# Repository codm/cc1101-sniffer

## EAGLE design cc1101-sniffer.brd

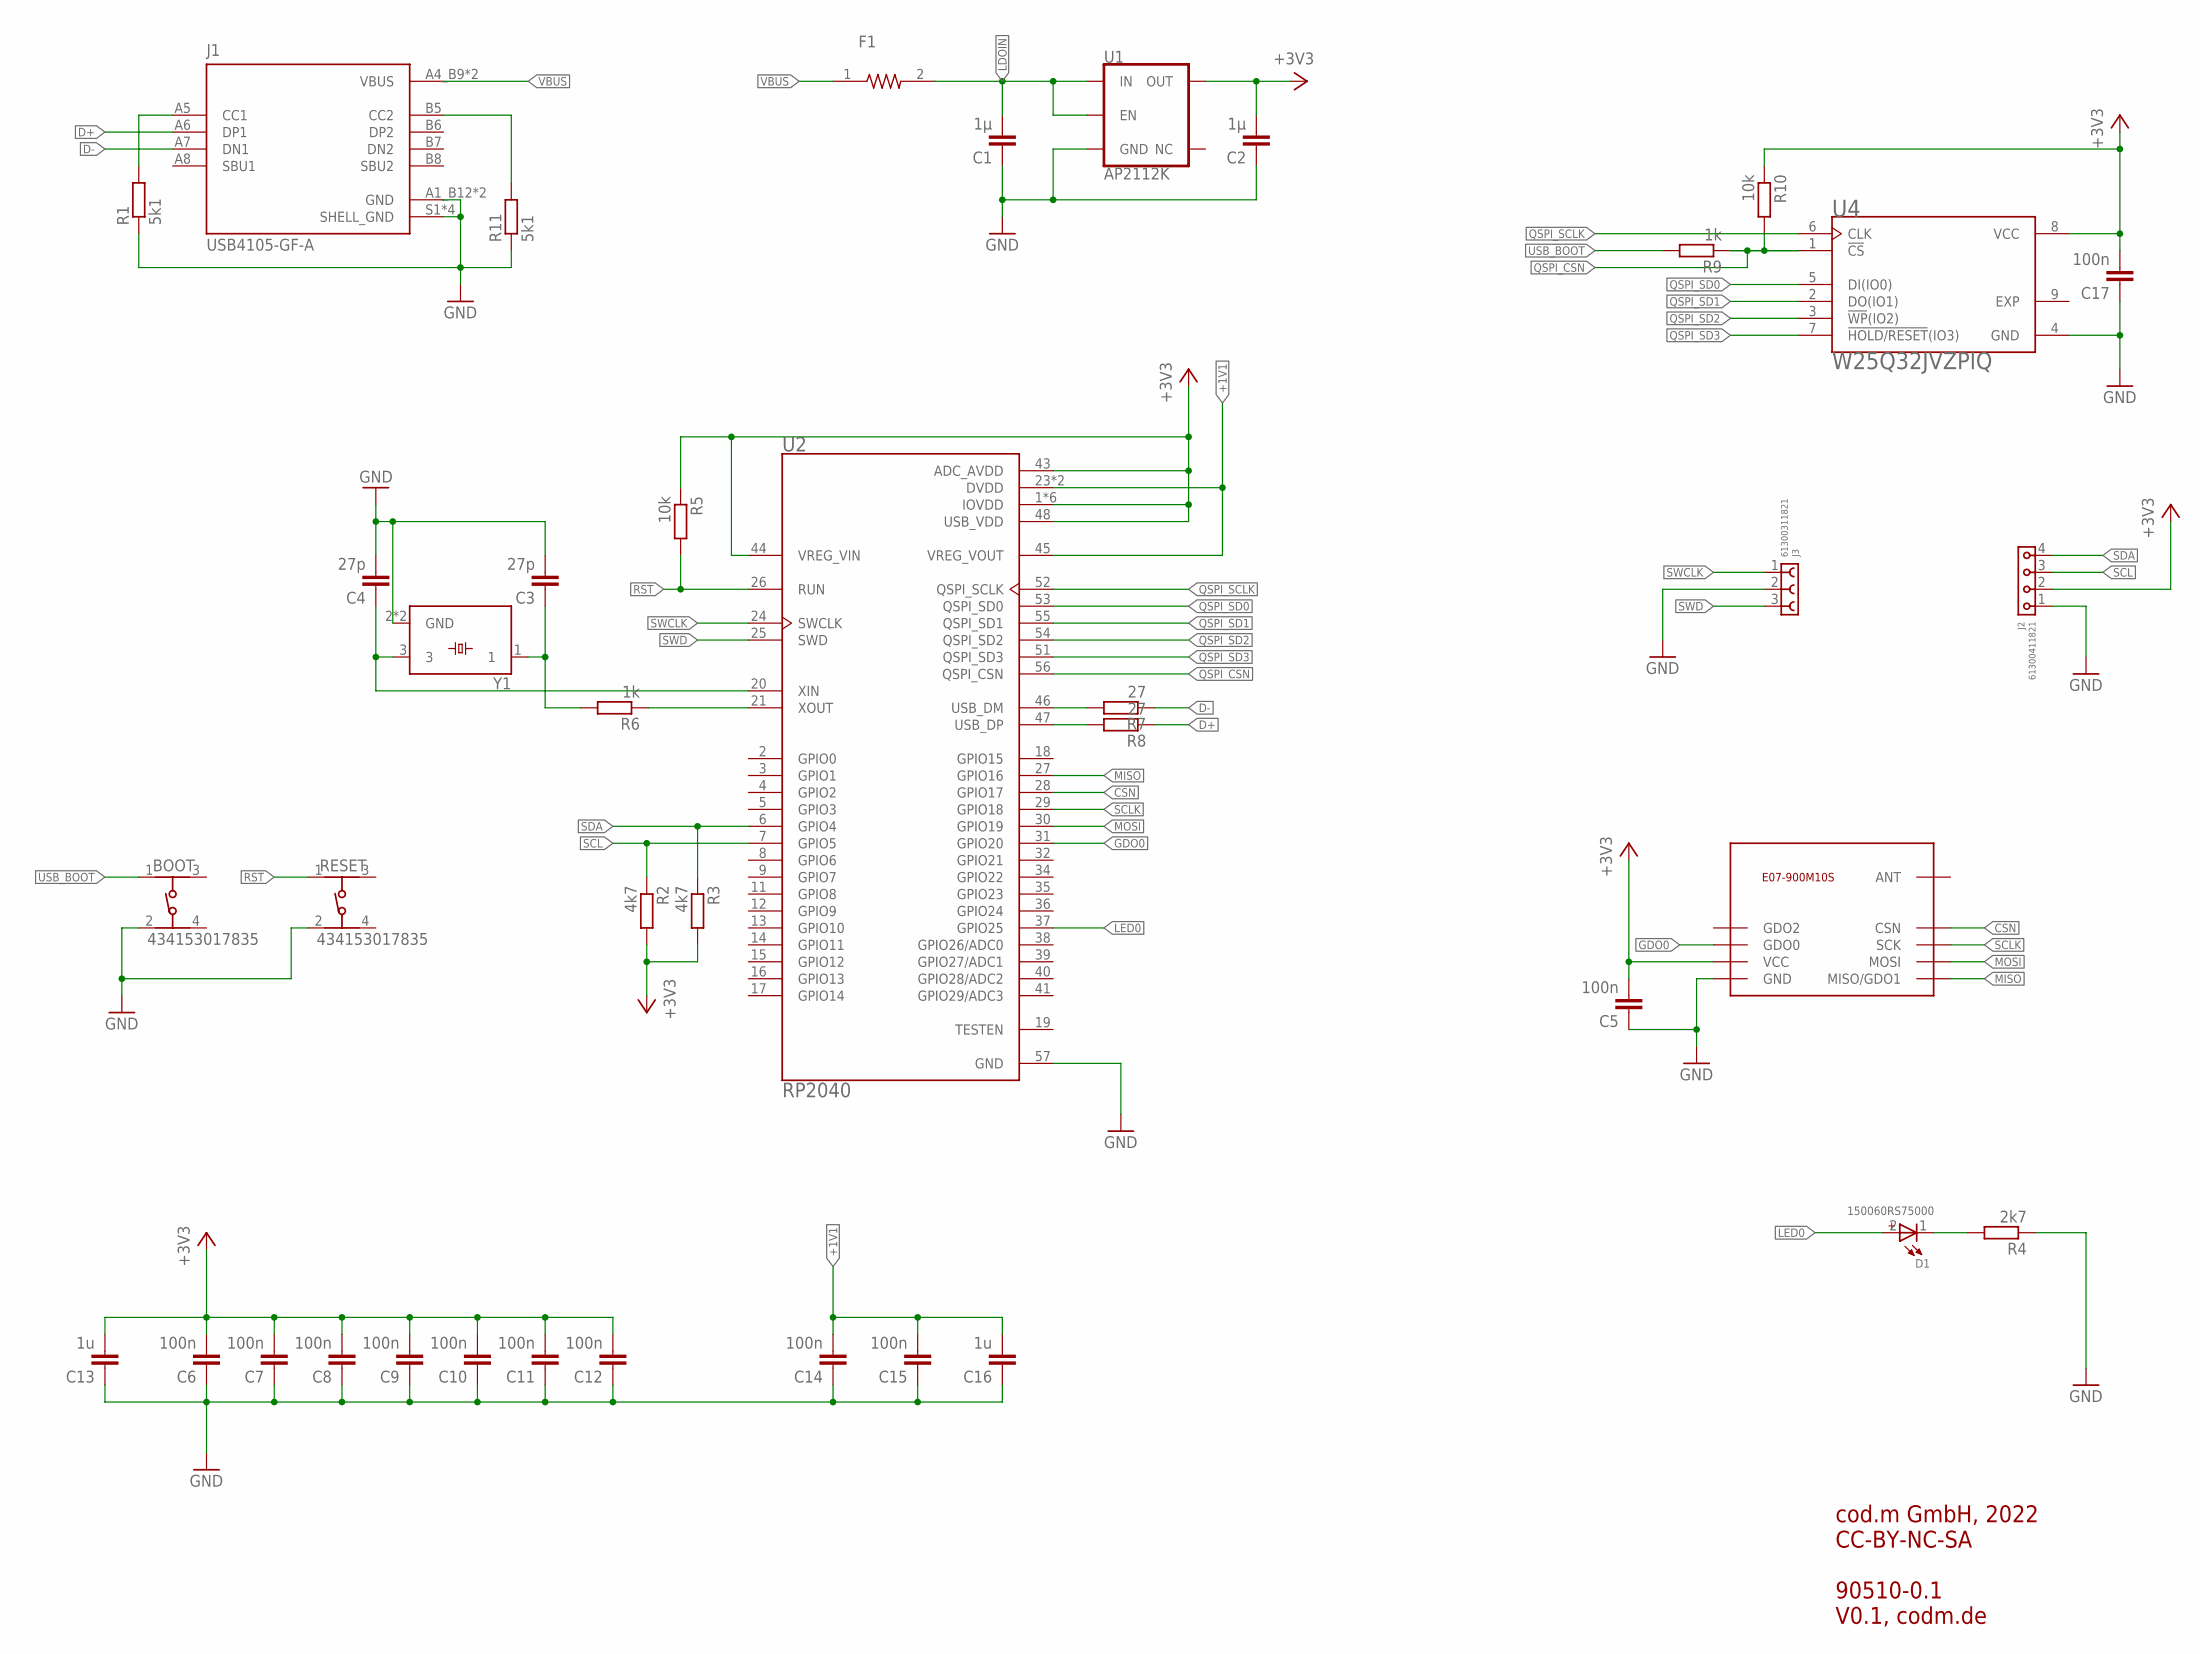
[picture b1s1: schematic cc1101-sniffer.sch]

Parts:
BOOT: 434153017835
C1, C2: 1µ; C0805K
C3, C4: 27p; C0603K
C5, C6, C7, C8, C9, C10, C11, C12, C14, C15, C17: 100n; C0603K
C13, C16: 1u; C0603K
D1: 150060RS75000; WL-SMCW_0603
F1: PICOSMDC050S-2; RESC2012X65N
J1: USB4105-GF-A; GCT_USB4105-GF-A
J2: 61300411821
J3: 61300311821
R1, R11: 5k1; R0603RF
R2, R3: 4k7; R0603RF
R4: 2k7; R0603RF
R5, R10: 10k; R0603RF
R6, R9: 1k; R0603RF
R7, R8: 27; R0603RF
RESET: 434153017835
U1: AP2112K; SOT23-5
U2: RP2040; QFN40P700X700X90-57N
U4: W25Q32JVZPIQ; SON127P600X500X80-9N
U$6: E07-900M10S
Y1: ABM8G-12.000MHZ-18-D2Y-T3; OSCSC320X250X100N

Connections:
+1V1: C14.2, C15.2, C16.2, U2.23 (DVDD), U2.45 (VREG_VOUT), U2.50 (DVDD)
+3V3: C2.2, C5.2, C6.2, C7.2, C8.2, C9.2, C10.2, C11.2, C12.2, C13.2, C17.2, J2.2, R2.2, R3.2, R5.1, R10.1, U1.5 (OUT), U2.1 (IOVDD), U2.10 (IOVDD), U2.22 (IOVDD), U2.33 (IOVDD), U2.42 (IOVDD), U2.43 (ADC_AVDD), U2.44 (VREG_VIN), U2.48 (USB_VDD), U2.49 (IOVDD), U4.8 (VCC), U$6.9 (VCC)
CSN: U2.28 (GPIO17), U$6.19 (CSN)
D+: J1.A6 (DP1), R8.1
D-: J1.A7 (DN1), R7.1
GDO0: U2.31 (GPIO20), U$6.15 (GDO0)
GND: BOOT.2 (3), C1.1, C2.1, C3.2, C4.2, C5.1, C6.1, C7.1, C8.1, C9.1, C10.1, C11.1, C12.1, C13.1, C14.1, C15.1, C16.1, C17.1, J1.A1_B12 (GND), J1.B1_A12 (GND), J1.S1 (SHELL_GND), J1.S2 (SHELL_GND), J1.S3 (SHELL_GND), J1.S4 (SHELL_GND), J2.1, J3.2, R1.1, R4.1, R11.1, RESET.2 (3), U1.2 (GND), U2.57 (GND), U4.4 (GND), U$6.1 (GND), U$6.2 (GND), U$6.3 (GND), U$6.4 (GND), U$6.5 (GND), U$6.11 (GND), U$6.12 (GND), U$6.20 (GND), U$6.22 (GND), Y1.2 (GND), Y1.4 (GND)
LDOIN: C1.2, F1.2, U1.1 (IN), U1.3 (EN)
LED0: D1.2 (+), U2.37 (GPIO25)
MISO: U2.27 (GPIO16), U$6.16 (MISO/GDO1)
MOSI: U2.30 (GPIO19), U$6.17 (MOSI)
unnamed: C4.1, U2.20 (XIN), Y1.3
unnamed: R6.1, U2.21 (XOUT)
unnamed: C3.1, R6.2, Y1.1
unnamed: R8.2, U2.47 (USB_DP)
unnamed: J1.A5 (CC1), R1.2
unnamed: D1.1 (-), R4.2
unnamed: R7.2, U2.46 (USB_DM)
unnamed: J1.B5 (CC2), R11.2
QSPI_CSN: R9.1, R10.2, U2.56 (QSPI_CSN), U4.1 (!CS)
QSPI_SCLK: U2.52 (QSPI_SCLK), U4.6 (CLK)
QSPI_SD0: U2.53 (QSPI_SD0), U4.5 (DI(IO0))
QSPI_SD1: U2.55 (QSPI_SD1), U4.2 (DO(IO1))
QSPI_SD2: U2.54 (QSPI_SD2), U4.3 (!WP!(IO2))
QSPI_SD3: U2.51 (QSPI_SD3), U4.7 (!HOLD/RESET!(IO3))
RST: R5.2, RESET.1, U2.26 (RUN)
SCL: J2.3, R2.1, U2.7 (GPIO5)
SCLK: U2.29 (GPIO18), U$6.18 (SCK)
SDA: J2.4, R3.1, U2.6 (GPIO4)
SWCLK: J3.1, U2.24 (SWCLK)
SWD: J3.3, U2.25 (SWD)
USB_BOOT: BOOT.1, R9.2
VBUS: F1.1, J1.A4_B9 (VBUS), J1.B4_A9 (VBUS)

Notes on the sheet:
cod.m GmbH, 2022 CC-BY-NC-SA 90510-0.1 V0.1, codm.de

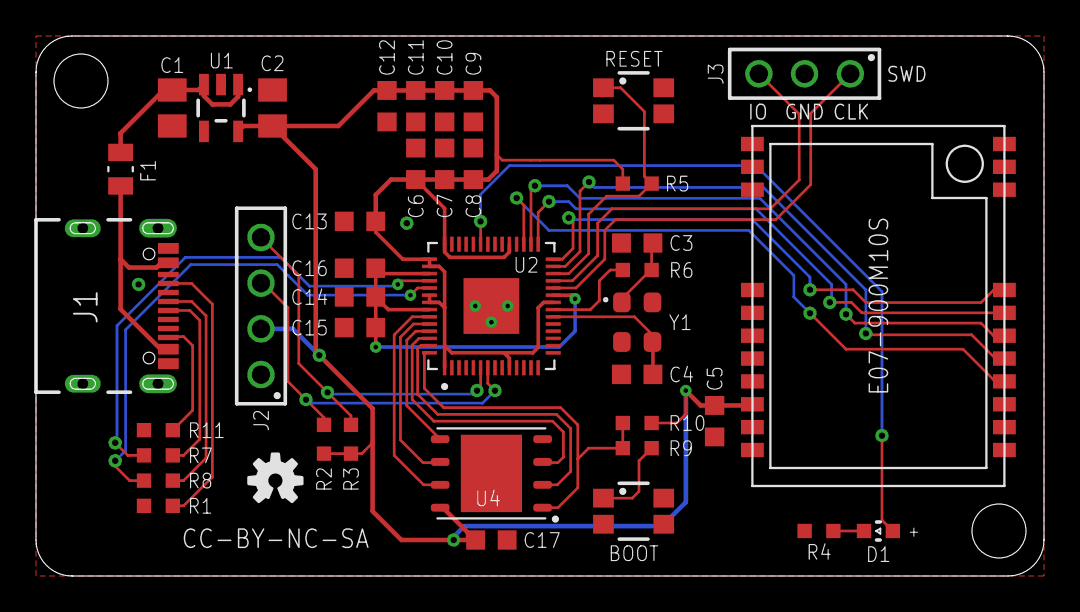
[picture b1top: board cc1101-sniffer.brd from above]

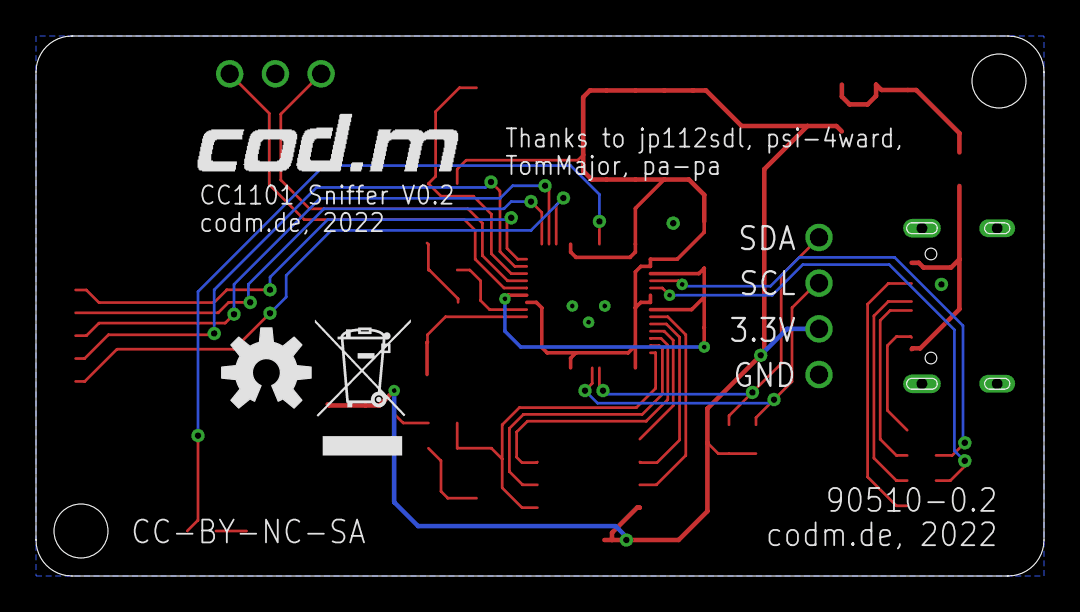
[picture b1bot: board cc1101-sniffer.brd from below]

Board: 2 copper layers, 56.0 x 30.0 mm, 44 parts (3 on the bottom side), 33 nets.

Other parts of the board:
U$1: WEEE-LOGO-5MM
U$3: OSHW-LOGO-M
U$4: OSHW-LOGO-S
U$5: CODM-LOGO

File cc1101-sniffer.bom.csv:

"Qty";"Value";"Device";"Package";"Parts";"Description";"AVAILABILITY";"CHIP-TECHNOLOGY";"DATASHEET-URL";"DESCRIPTION";"DOMINANT-WAVELENGTH";"EMITTING-COLOR";"FORWARD-VOLTAGE";"GENDER";"H";"IR";"LUMINOUS-INTENSITY";"MF";"MOUNT";"MP";"OPERATION-FORCE";"PACKAGE";"PACKAGING";"PART-NUMBER";"PEAK-WAVELENGTH";"PINS";"PITCH";"POPULARITY";"PRICE";"PROD_ID";"PURCHASE-URL";"QTY";"ROWS";"SPICEPREFIX";"TYPE";"VALUE";
"1";"";"ANTENNA_U.FL";"U.FL";"X1";"U.FL Antenna Connector";"";"";"";"";"";"";"";"";"";"";"";"";"";"";"";"";"";"";"";"";"";"";"";"";"";"";"";"";"";"";
"1";" 61300311821 ";"6130XX11821_61300311821";"61300311821";"J3";"WR-PHD 2.54 mm Socket Header";"";"";"https://www.we-online.com/catalog/datasheet/61300311821.pdf";"";"";"";"";"Socket Header";"";"3A";"";"";"THT";"";"";"";"Tray";" 61300311821 ";"";" 3 ";"2.54mm";"";"";"";"";"";"Single";"";"Straight";" 61300311821 ";
"1";" 61300411821 ";"6130XX11821_61300411821";"61300411821";"J2";"WR-PHD 2.54 mm Socket Header";"";"";"https://www.we-online.com/catalog/datasheet/61300411821.pdf";"";"";"";"";"Socket Header";"";"3A";"";"";"THT";"";"";"";"Tray";" 61300411821 ";"";" 4 ";"2.54mm";"";"";"";"";"";"Single";"";"Straight";" 61300411821 ";
"11";"100n";"C-EUC0603K";"C0603K";"C5, C6, C7, C8, C9, C10, C11, C12, C14, C15, C17";"CAPACITOR, European symbol";"";"";"";"";"";"";"";"";"";"";"";"";"";"";"";"";"";"";"";"";"";"30";"";"";"";"";"";"C";"";"";
"2";"10k";"R-EU_R0603RF";"R0603RF";"R5, R10";"";"";"";"";"";"";"";"";"";"";"";"";"";"";"";"";"";"";"";"";"";"";"";"";"";"";"";"";"";"";"";
"1";"150060RS75000";"WL-SMCW_0603_150060RS75000";"WL-SMCW_0603";"D1";"WL-SMCW SMT Mono-color Chip LED Waterclea";"";"AlInGaP";"https://www.we-online.com/catalog/datasheet/150060RS75000.pdf";"";"625nm";"Red";"140°";"";"";"";"250mcd";"";"";"";"";"";"";"150060RS75000";"630nm";"";"";"";"";"";"";"";"";"";"";"150060RS75000";
"3";"1k";"R-EU_R0603RF";"R0603RF";"R4, R6, R9";"";"";"";"";"";"";"";"";"";"";"";"";"";"";"";"";"";"";"";"";"";"";"";"";"";"";"";"";"";"";"";
"2";"1u";"C-EUC0603K";"C0603K";"C13, C16";"CAPACITOR, European symbol";"";"";"";"";"";"";"";"";"";"";"";"";"";"";"";"";"";"";"";"";"";"30";"";"";"";"";"";"C";"";"";
"2";"1µ";"C-EUC0805K";"C0805K";"C1, C2";"CAPACITOR, European symbol";"";"";"";"";"";"";"";"";"";"";"";"";"";"";"";"";"";"";"";"";"";"52";"";"";"";"";"";"C";"";"";
"2";"27";"R-EU_R0603RF";"R0603RF";"R7, R8";"";"";"";"";"";"";"";"";"";"";"";"";"";"";"";"";"";"";"";"";"";"";"";"";"";"";"";"";"";"";"";
"2";"27p";"C-EUC0603K";"C0603K";"C3, C4";"CAPACITOR, European symbol";"";"";"";"";"";"";"";"";"";"";"";"";"";"";"";"";"";"";"";"";"";"30";"";"";"";"";"";"C";"";"";
"2";"434153017835";"434153017835";"434153017835";"BOOT, RESET";"WS-TASV J-Bend SMT Tact Switch 3.5x2.9 mm";"";"";"https://www.we-online.com/catalog/datasheet/434153017835.pdf";"";"";"";"";"";"1.7mm";"";"";"";"";"";"350g";"";"";"434153017835";"";"";"";"";"";"";"";" 4000 ";"";"";"";"434153017835";
"2";"4k7";"R-EU_R0603RF";"R0603RF";"R2, R3";"";"";"";"";"";"";"";"";"";"";"";"";"";"";"";"";"";"";"";"";"";"";"";"";"";"";"";"";"";"";"";
"2";"5k1";"R-EU_R0603RF";"R0603RF";"R1, R11";"";"";"";"";"";"";"";"";"";"";"";"";"";"";"";"";"";"";"";"";"";"";"";"";"";"";"";"";"";"";"";
"1";"ABM8G-12.000MHZ-18-D2Y-T3";"ABM8G-12.000MHZ-18-D2Y-T3";"OSCSC320X250X100N";"Y1";"Crystal 20MHz Â±20ppm (Tol) Â±30ppm (Stability) 18pF FUND 80Ohm 4-Pin Mini-CSMD T/R Check availability";"In Stock";"";"";" 12 MHz ±20ppm Crystal 18pF 120 Ohms 4-SMD, No Lead ";"";"";"";"";"";"";"";"Abracon";"";"ABM8G-12.000MHZ-18-D2Y-T3";"";"SMD-4 Abracon";"";"";"";"";"";"";"None";"";"https://pricing.snapeda.com/search/part/ABM8G-12.000MHZ-18-D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";"";"";"";"";"";
"1";"AP2112K";"V_REG_AP2112K-3.3V";"SOT23-5";"U1";"AP2112 - 600mA CMOS LDO Regulator w/ Enable";"";"";"";"";"";"";"";"";"";"";"";"";"";"";"";"";"";"";"";"";"";"";"";"VREG-12457";"";"";"";"";"";"3.3V";
"1";"CC1101-868MS10";"CC1101-868MS10";"CC1101-868MS10";"U$2";"";"";"";"";"";"";"";"";"";"";"";"";"";"";"";"";"";"";"";"";"";"";"";"";"";"";"";"";"";"";"";
"1";"PICOSMDC050S-2";"PICOSMDC050S-2";"RESC2012X65N";"F1";"FUSE, RESETTABLE PTC, 6VDC, 0.5A, SMD Check availability";"In Stock";"";"";" Polymeric PTC Resettable Fuse 6V 500 mA Ih Surface Mount 0805 (2012 Metric), Concave ";"";"";"";"";"";"";"";"Littelfuse Inc.";"";"PICOSMDC050S-2";"";"0805 TE Connectivity";"";"";"";"";"";"";"None";"";"https://pricing.snapeda.com/search/part/PICOSMDC050S-2/?ref=eda";"";"";"";"";"";
"1";"RP2040";"RP2040";"QFN40P700X700X90-57N";"U2";"Check availability";"In Stock";"";"";" RP2040 chip for Raspberry Pi Pico - ARM® Cortex®-M0+ MCU 32-Bit ";"";"";"";"";"";"";"";"Raspberry Pi";"";"RP2040";"";"Package ";"";"";"";"";"";"";"None";"";"https://pricing.snapeda.com/search/part/RP2040/?ref=eda";"";"";"";"";"";
"1";"USB4105-GF-A";"USB4105-GF-A";"GCT_USB4105-GF-A";"J1";"USB-C (USB TYPE-C) USB 2.0 Receptacle Connector 24 (16+8 Dummy) Position Surface Mount, Right Angle; Through Hole  Check availability";"In Stock";"";"";" USB-C (USB TYPE-C) USB 2.0 Receptacle Connector 24 (16+8 Dummy) Position Surface Mount, Right Angle";" Through Hole ";"";"";"";"";"";"";"";"GCT";"";"USB4105-GF-A";"";"None";"";"";"";"";"";"";"None";"";"https://pricing.snapeda.com/search/part/USB4105-GF-A/?ref=eda";"";"";"";"";
"1";"W25Q32JVZPIQ";"W25Q32JVZPIQ";"SON127P600X500X80-9N";"U4";"Serial Flash Memory With Dual, Quad Spi Check availability";"In Stock";"";"";" FLASH - NOR Memory IC 32Mb (4M x 8) SPI - Quad I/O 133 MHz 8-WSON (6x5) ";"";"";"";"";"";"";"";"Winbond";"";"W25Q32JVZPIQ";"";"WSON-8 Winbond";"";"";"";"";"";"";"None";"";"https://pricing.snapeda.com/search/part/W25Q32JVZPIQ/?ref=eda";"";"";"";"";"";

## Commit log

2022-03-03 WIP first version
2022-04-12 tCream for USB and E01-900M10S

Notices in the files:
parts and their libraries:
SparkFun-IC-Power: Licensing: Creative Commons ShareAlike 4.0 International - https://creativecommons.org/licenses/by-sa/4.0
Eagle_WR-PHD: Copyright: Würth Elektronik
